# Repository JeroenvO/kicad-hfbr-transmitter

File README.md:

KiCad scheme and pcb for a HFBR transmitter circuit using a PYNQ fpga with arduino pinout (or to use with arduino directly)
Using SOT-343 bjt npn transistors and SMD 1206 resistors/capacitors.

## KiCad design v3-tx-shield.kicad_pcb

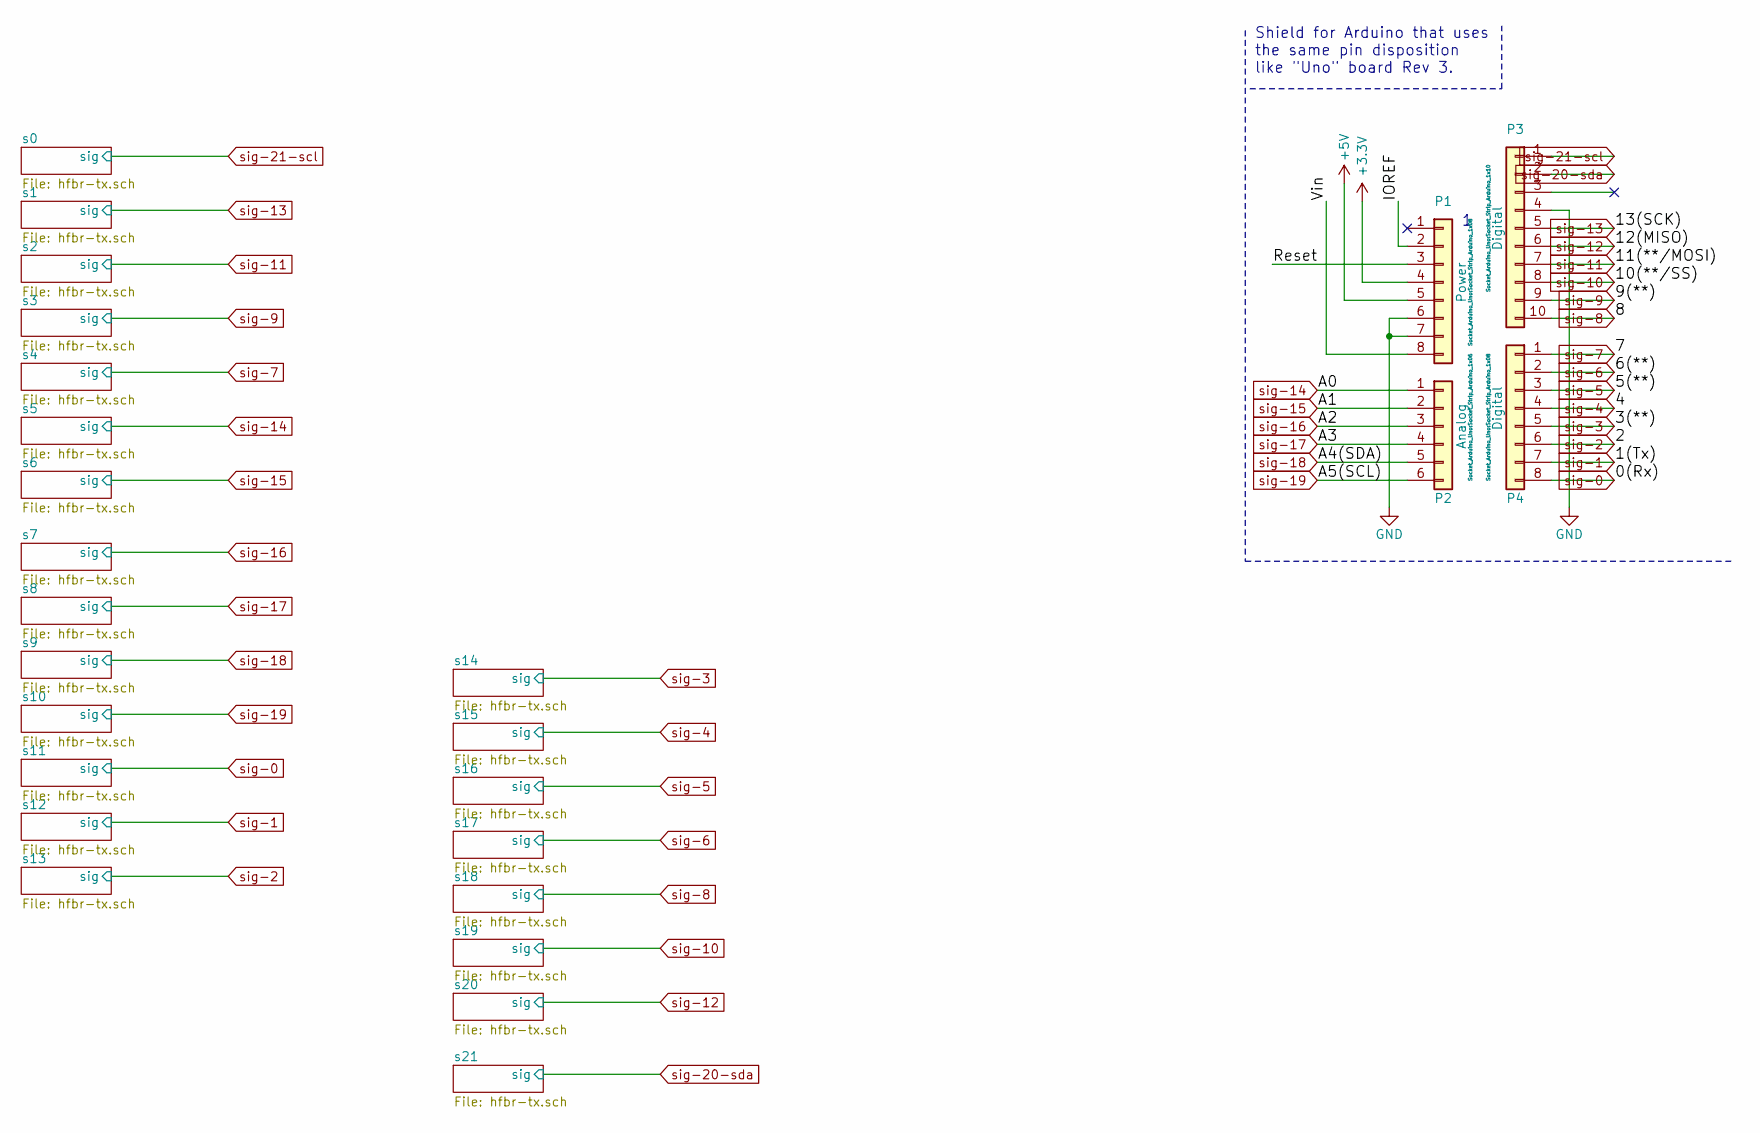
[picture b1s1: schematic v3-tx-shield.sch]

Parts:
P1: Power; Socket_Strip_Arduino_1x08
P2: Analog; Socket_Strip_Arduino_1x06
P3: Digital; Socket_Strip_Arduino_1x10
P4: Digital; Socket_Strip_Arduino_1x08

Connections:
+3V3: P1.4
+5V: P1.5; also elsewhere on the board
/IOREF: P1.2
/Reset: P1.3
/Vin: P1.8
GND: P1.6, P1.7, P3.4; also elsewhere on the board
sig-0: P4.8; also elsewhere on the board
sig-1: P4.7; also elsewhere on the board
sig-2: P4.6; also elsewhere on the board
sig-3: P4.5; also elsewhere on the board
sig-4: P4.4; also elsewhere on the board
sig-5: P4.3; also elsewhere on the board
sig-6: P4.2; also elsewhere on the board
sig-7: P4.1; also elsewhere on the board
sig-8: P3.10; also elsewhere on the board
sig-9: P3.9; also elsewhere on the board
sig-10: P3.8; also elsewhere on the board
sig-11: P3.7; also elsewhere on the board
sig-12: P3.6; also elsewhere on the board
sig-13: P3.5; also elsewhere on the board
sig-14: P2.1; also elsewhere on the board
sig-15: P2.2; also elsewhere on the board
sig-16: P2.3; also elsewhere on the board
sig-17: P2.4; also elsewhere on the board
sig-18: P2.5; also elsewhere on the board
sig-19: P2.6; also elsewhere on the board
sig-20-sda: P3.2; also elsewhere on the board
sig-21-scl: P3.1; also elsewhere on the board

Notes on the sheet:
Shield for Arduino that uses the same pin disposition like "Uno" board Rev 3.

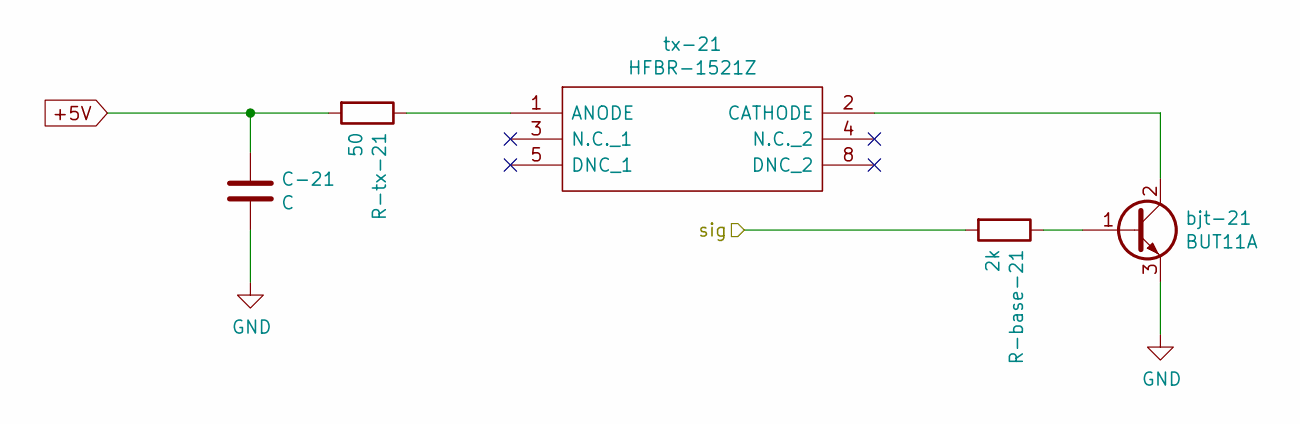
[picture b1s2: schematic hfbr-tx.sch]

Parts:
C-13: C; C_1206_3216Metric_Pad1.42x1.75mm_HandSolder
R-base-0: 2k; R_1206_3216Metric_Pad1.42x1.75mm_HandSolder
R-tx-0: 50; R_1206_3216Metric_Pad1.42x1.75mm_HandSolder
bjt-0: BUT11A; SOT-343_SC-70-4_Handsoldering
tx-0: HFBR-1521Z; HFBR1521Z; Mouser Part Number 630-HFBR-1521Z

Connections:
+5V: C-13.1, R-tx-0.2; also elsewhere on the board
GND: C-13.2, bjt-0.3 (E); also elsewhere on the board
unnamed: R-base-0.1, bjt-0.1 (B)
unnamed: R-tx-0.1, tx-0.1 (ANODE)
unnamed: bjt-0.2 (C), tx-0.2 (CATHODE)
sig-21-scl: R-base-0.2; also elsewhere on the board

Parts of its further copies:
C-0, C-1, C-2, C-3, C-4, C-5, C-6, C-7, C-8, C-9, C-10, C-11, C-12, C-14, C-15, C-16, C-17, C-18, C-19, C-20, C-21: C; C_1206_3216Metric_Pad1.42x1.75mm_HandSolder
R-base-1, R-base-2, R-base-3, R-base-4, R-base-5, R-base-6, R-base-7, R-base-8, R-base-9, R-base-10, R-base-11, R-base-12, R-base-13, R-base-14, R-base-15, R-base-16, R-base-17, R-base-18, R-base-19, R-base-20, R-base-21: 2k; R_1206_3216Metric_Pad1.42x1.75mm_HandSolder
R-tx-1, R-tx-2, R-tx-3, R-tx-4, R-tx-5, R-tx-6, R-tx-7, R-tx-8, R-tx-9, R-tx-10, R-tx-11, R-tx-12, R-tx-13, R-tx-14, R-tx-15, R-tx-16, R-tx-17, R-tx-18, R-tx-19, R-tx-20, R-tx-21: 50; R_1206_3216Metric_Pad1.42x1.75mm_HandSolder
bjt-1, bjt-2, bjt-3, bjt-4, bjt-5, bjt-6, bjt-7, bjt-8, bjt-9, bjt-10, bjt-11, bjt-12, bjt-13, bjt-14, bjt-15, bjt-16, bjt-17, bjt-18, bjt-19, bjt-20, bjt-21: BUT11A; SOT-343_SC-70-4_Handsoldering
tx-1, tx-2, tx-3, tx-4, tx-5, tx-6, tx-7, tx-8, tx-9, tx-10, tx-11, tx-12, tx-13, tx-14, tx-15, tx-16, tx-17, tx-18, tx-19, tx-20, tx-21: HFBR-1521Z; HFBR1521Z; Mouser Part Number 630-HFBR-1521Z

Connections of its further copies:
+5V: C-0.1, C-1.1, C-2.1, C-3.1, C-4.1, C-5.1, C-6.1, C-7.1, C-8.1, C-9.1, C-10.1, C-11.1, C-12.1, C-14.1, C-15.1, C-16.1, C-17.1, C-18.1, C-19.1, C-20.1, C-21.1, R-tx-1.2, R-tx-2.2, R-tx-3.2, R-tx-4.2, R-tx-5.2, R-tx-6.2, R-tx-7.2, R-tx-8.2, R-tx-9.2, R-tx-10.2, R-tx-11.2, R-tx-12.2, R-tx-13.2, R-tx-14.2, R-tx-15.2, R-tx-16.2, R-tx-17.2, R-tx-18.2, R-tx-19.2, R-tx-20.2, R-tx-21.2; also elsewhere on the board
GND: C-0.2, C-1.2, C-2.2, C-3.2, C-4.2, C-5.2, C-6.2, C-7.2, C-8.2, C-9.2, C-10.2, C-11.2, C-12.2, C-14.2, C-15.2, C-16.2, C-17.2, C-18.2, C-19.2, C-20.2, C-21.2, bjt-1.3 (E), bjt-2.3 (E), bjt-3.3 (E), bjt-4.3 (E), bjt-5.3 (E), bjt-6.3 (E), bjt-7.3 (E), bjt-8.3 (E), bjt-9.3 (E), bjt-10.3 (E), bjt-11.3 (E), bjt-12.3 (E), bjt-13.3 (E), bjt-14.3 (E), bjt-15.3 (E), bjt-16.3 (E), bjt-17.3 (E), bjt-18.3 (E), bjt-19.3 (E), bjt-20.3 (E), bjt-21.3 (E); also elsewhere on the board
unnamed: R-base-1.1, bjt-1.1 (B)
unnamed: R-base-2.1, bjt-2.1 (B)
unnamed: R-base-3.1, bjt-3.1 (B)
unnamed: R-base-4.1, bjt-4.1 (B)
unnamed: R-base-5.1, bjt-5.1 (B)
unnamed: R-base-6.1, bjt-6.1 (B)
unnamed: R-base-7.1, bjt-7.1 (B)
unnamed: R-base-8.1, bjt-8.1 (B)
unnamed: R-base-9.1, bjt-9.1 (B)
unnamed: R-base-10.1, bjt-10.1 (B)
unnamed: R-base-11.1, bjt-11.1 (B)
unnamed: R-base-12.1, bjt-12.1 (B)
unnamed: R-base-13.1, bjt-13.1 (B)
unnamed: R-base-14.1, bjt-14.1 (B)
unnamed: R-base-15.1, bjt-15.1 (B)
unnamed: R-base-16.1, bjt-16.1 (B)
unnamed: R-base-17.1, bjt-17.1 (B)
unnamed: R-base-18.1, bjt-18.1 (B)
unnamed: R-base-19.1, bjt-19.1 (B)
unnamed: R-base-20.1, bjt-20.1 (B)
unnamed: R-base-21.1, bjt-21.1 (B)
unnamed: R-tx-1.1, tx-1.1 (ANODE)
unnamed: R-tx-2.1, tx-2.1 (ANODE)
unnamed: R-tx-3.1, tx-3.1 (ANODE)
unnamed: R-tx-4.1, tx-4.1 (ANODE)
unnamed: R-tx-5.1, tx-5.1 (ANODE)
unnamed: R-tx-6.1, tx-6.1 (ANODE)
unnamed: R-tx-7.1, tx-7.1 (ANODE)
unnamed: R-tx-8.1, tx-8.1 (ANODE)
unnamed: R-tx-9.1, tx-9.1 (ANODE)
unnamed: R-tx-10.1, tx-10.1 (ANODE)
unnamed: R-tx-11.1, tx-11.1 (ANODE)
unnamed: R-tx-12.1, tx-12.1 (ANODE)
unnamed: R-tx-13.1, tx-13.1 (ANODE)
unnamed: R-tx-14.1, tx-14.1 (ANODE)
unnamed: R-tx-15.1, tx-15.1 (ANODE)
unnamed: R-tx-16.1, tx-16.1 (ANODE)
unnamed: R-tx-17.1, tx-17.1 (ANODE)
unnamed: R-tx-18.1, tx-18.1 (ANODE)
unnamed: R-tx-19.1, tx-19.1 (ANODE)
unnamed: R-tx-20.1, tx-20.1 (ANODE)
unnamed: R-tx-21.1, tx-21.1 (ANODE)
unnamed: bjt-1.2 (C), tx-1.2 (CATHODE)
unnamed: bjt-2.2 (C), tx-2.2 (CATHODE)
unnamed: bjt-3.2 (C), tx-3.2 (CATHODE)
unnamed: bjt-4.2 (C), tx-4.2 (CATHODE)
unnamed: bjt-5.2 (C), tx-5.2 (CATHODE)
unnamed: bjt-6.2 (C), tx-6.2 (CATHODE)
unnamed: bjt-7.2 (C), tx-7.2 (CATHODE)
unnamed: bjt-8.2 (C), tx-8.2 (CATHODE)
unnamed: bjt-9.2 (C), tx-9.2 (CATHODE)
unnamed: bjt-10.2 (C), tx-10.2 (CATHODE)
unnamed: bjt-11.2 (C), tx-11.2 (CATHODE)
unnamed: bjt-12.2 (C), tx-12.2 (CATHODE)
unnamed: bjt-13.2 (C), tx-13.2 (CATHODE)
unnamed: bjt-14.2 (C), tx-14.2 (CATHODE)
unnamed: bjt-15.2 (C), tx-15.2 (CATHODE)
unnamed: bjt-16.2 (C), tx-16.2 (CATHODE)
unnamed: bjt-17.2 (C), tx-17.2 (CATHODE)
unnamed: bjt-18.2 (C), tx-18.2 (CATHODE)
unnamed: bjt-19.2 (C), tx-19.2 (CATHODE)
unnamed: bjt-20.2 (C), tx-20.2 (CATHODE)
unnamed: bjt-21.2 (C), tx-21.2 (CATHODE)
sig-0: R-base-11.2; also elsewhere on the board
sig-1: R-base-12.2; also elsewhere on the board
sig-2: R-base-13.2; also elsewhere on the board
sig-3: R-base-14.2; also elsewhere on the board
sig-4: R-base-15.2; also elsewhere on the board
sig-5: R-base-16.2; also elsewhere on the board
sig-6: R-base-17.2; also elsewhere on the board
sig-7: R-base-4.2; also elsewhere on the board
sig-8: R-base-18.2; also elsewhere on the board
sig-9: R-base-3.2; also elsewhere on the board
sig-10: R-base-19.2; also elsewhere on the board
sig-11: R-base-2.2; also elsewhere on the board
sig-12: R-base-20.2; also elsewhere on the board
sig-13: R-base-1.2; also elsewhere on the board
sig-14: R-base-5.2; also elsewhere on the board
sig-15: R-base-6.2; also elsewhere on the board
sig-16: R-base-7.2; also elsewhere on the board
sig-17: R-base-8.2; also elsewhere on the board
sig-18: R-base-9.2; also elsewhere on the board
sig-19: R-base-10.2; also elsewhere on the board
sig-20-sda: R-base-21.2; also elsewhere on the board

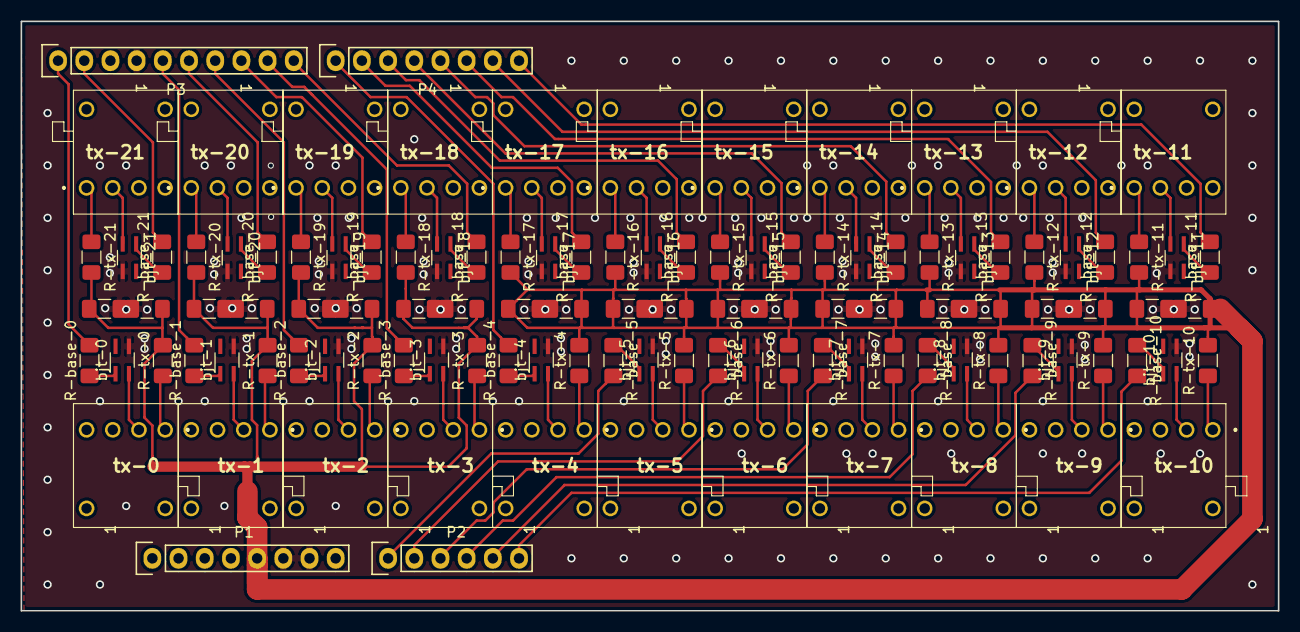
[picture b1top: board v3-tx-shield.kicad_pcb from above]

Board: 2 copper layers, 121.9 x 57.2 mm, 114 parts (0 on the bottom side), 90 nets.

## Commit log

2019-03-08 Initial
2019-04-02 Final version
